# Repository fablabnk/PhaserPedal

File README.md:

This was a project to build a [Phaser Guitar Pedal from Instructables](https://www.instructables.com/Phaser-Guitar-Pedal/). 

As we attempted the project, we found that the build steps in the photos were incomplete, so it is actually impossible to place all components and make all the solder connections on the protoboard in the same way they did.

Our solution was to attempt to rework a new layout directly from the schematic in KiCad, partly as a learning experience in how to use KiCad at all. This involved:

- recreating the schematic in the schematic editor
- creating a board template in the pcb editor and placing components as similarly as possible to the original project
- routing the rats nest
- using the routings as a template for soldering

- some connections are done with solder bridges, some with wires - the wires are the traces - but how did we do solder bridges again?

The current state of the project is that the circuit doesn't work and we're not sure why. One wire got disconnected so this could help.

A possible next step could be to manufacture a PCB, but we have no guarantee that we routed it correctly or that the project even works in the first place.

So it would be better to go back to first principles to understand the concepts in the circuit

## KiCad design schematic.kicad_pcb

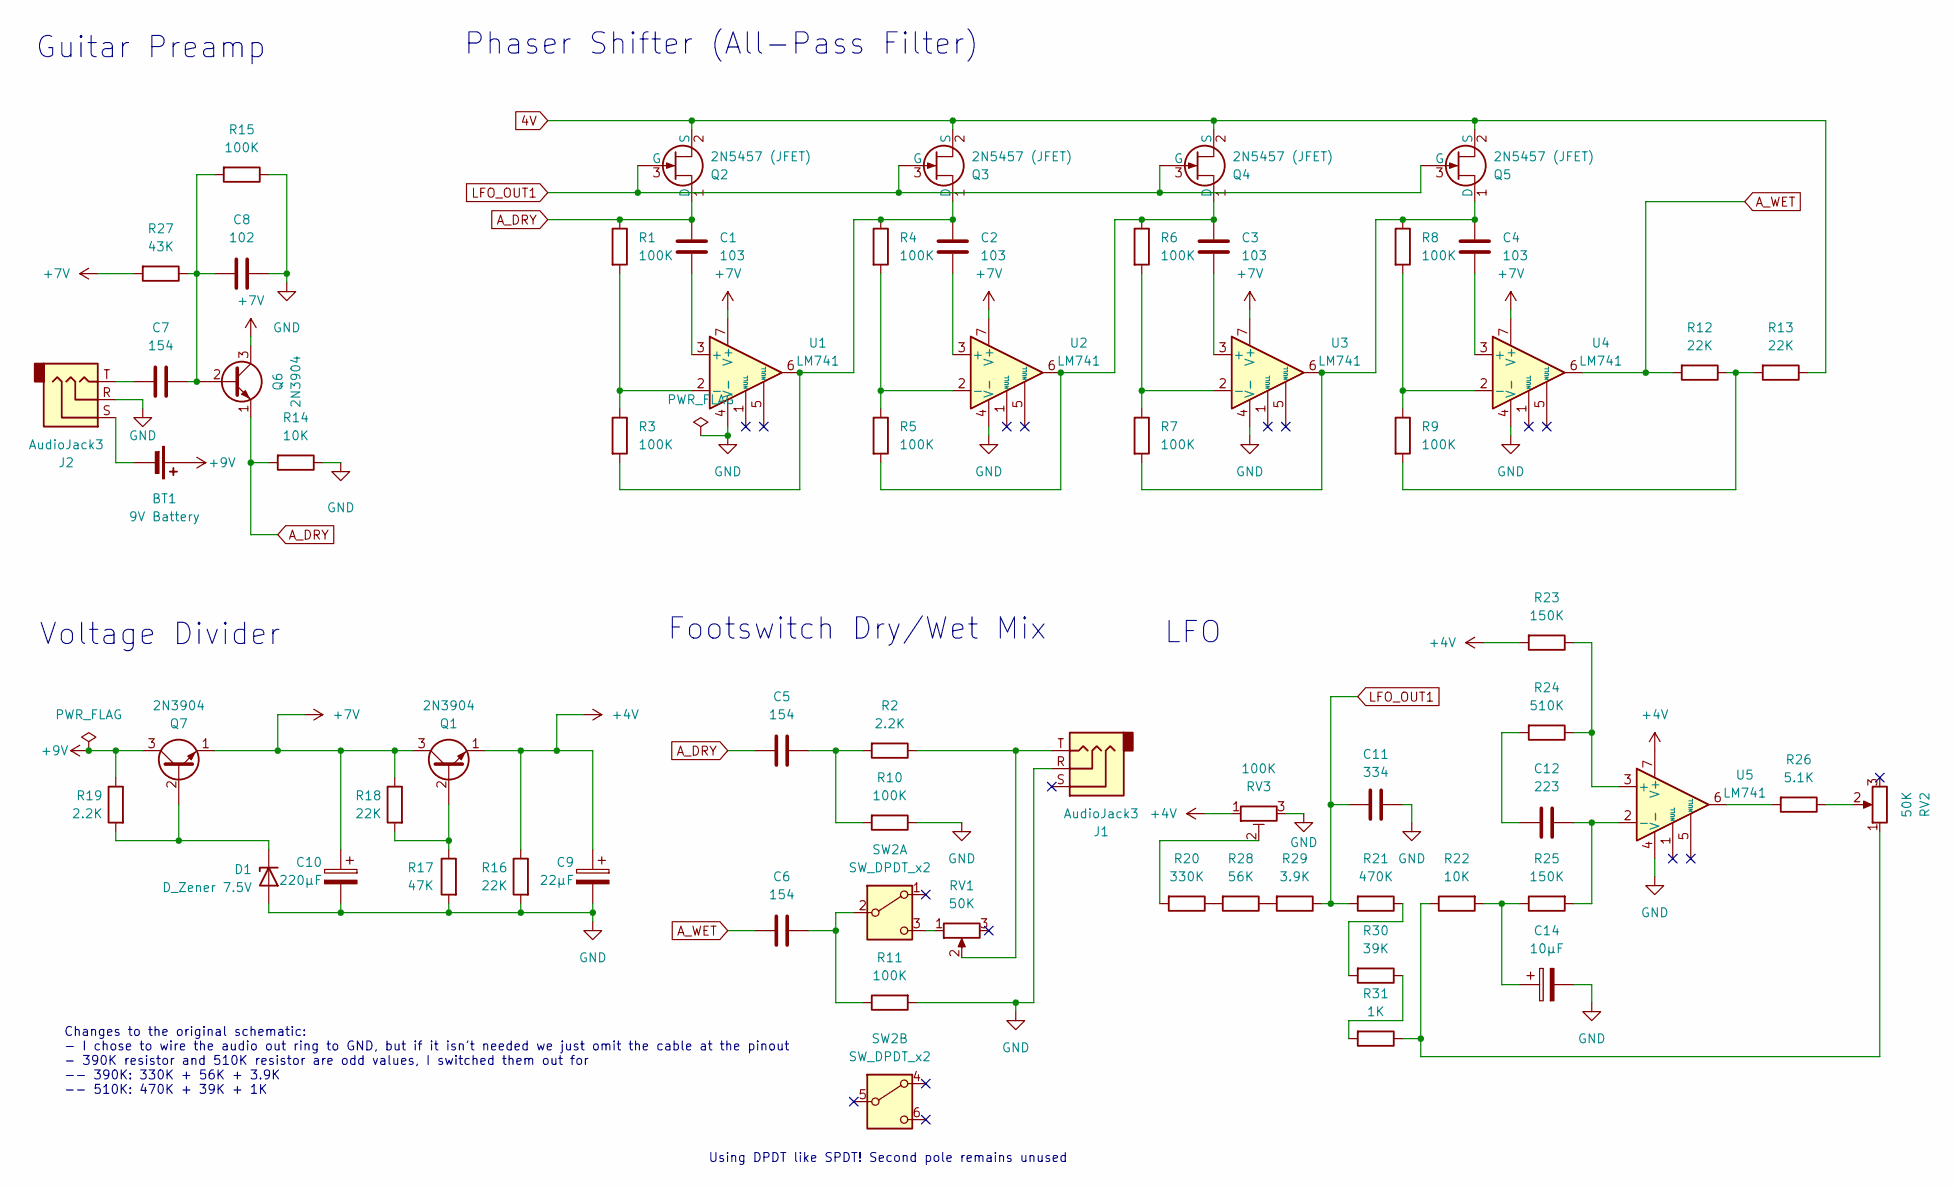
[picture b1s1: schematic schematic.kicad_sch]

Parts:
BT1: 9V Battery; PinHeader_1x02_P2.54mm_Vertical
C1, C2, C3, C4: 103; C_Axial_L5.1mm_D3.1mm_P7.50mm_Horizontal
C5, C6, C7: 154; C_Disc_D3.0mm_W1.6mm_P2.50mm
C8: 102; C_Axial_L5.1mm_D3.1mm_P7.50mm_Horizontal
C9: 22µF; CP_Radial_D5.0mm_P2.50mm
C10: 220µF; CP_Radial_D10.0mm_P5.00mm
C11: 334; C_Disc_D3.0mm_W1.6mm_P2.50mm
C12: 223; C_Axial_L5.1mm_D3.1mm_P7.50mm_Horizontal
C14: 10µF; CP_Radial_D5.0mm_P2.50mm
D1: D_Zener 7.5V; D_A-405_P7.62mm_Horizontal
J1: AudioJack3; PinHeader_1x02_P2.54mm_Vertical_TR
J2: AudioJack3; PinHeader_1x03_P2.54mm_Vertical_TRS
Q1, Q6, Q7: 2N3904; TO-92_Inline_Wide
Q2, Q3, Q4, Q5: 2N5457 (JFET); TO-92_Inline_Wide
R1, R3, R4, R5, R6, R7, R8, R9, R10, R11, R15: 100K; R_Axial_DIN0204_L3.6mm_D1.6mm_P5.08mm_Horizontal
R2, R19: 2.2K; R_Axial_DIN0204_L3.6mm_D1.6mm_P5.08mm_Horizontal
R12, R13, R16, R18: 22K; R_Axial_DIN0204_L3.6mm_D1.6mm_P5.08mm_Horizontal
R14, R22: 10K; R_Axial_DIN0204_L3.6mm_D1.6mm_P5.08mm_Horizontal
R17: 47K; R_Axial_DIN0204_L3.6mm_D1.6mm_P5.08mm_Horizontal
R20: 330K; R_Axial_DIN0204_L3.6mm_D1.6mm_P5.08mm_Horizontal
R21: 470K; R_Axial_DIN0204_L3.6mm_D1.6mm_P5.08mm_Horizontal
R23, R25: 150K; R_Axial_DIN0204_L3.6mm_D1.6mm_P5.08mm_Horizontal
R24: 510K; R_Axial_DIN0204_L3.6mm_D1.6mm_P5.08mm_Horizontal
R26: 5.1K; R_Axial_DIN0204_L3.6mm_D1.6mm_P5.08mm_Horizontal
R27: 43K; R_Axial_DIN0204_L3.6mm_D1.6mm_P5.08mm_Horizontal
R28: 56K; R_Axial_DIN0204_L3.6mm_D1.6mm_P5.08mm_Horizontal
R29: 3.9K; R_Axial_DIN0204_L3.6mm_D1.6mm_P5.08mm_Horizontal
R30: 39K; R_Axial_DIN0204_L3.6mm_D1.6mm_P5.08mm_Horizontal
R31: 1K; R_Axial_DIN0204_L3.6mm_D1.6mm_P5.08mm_Horizontal
RV1, RV2: 50K; PinHeader_1x02_P2.54mm_Vertical
RV3: 100K; Potentiometer_Bourns_3296Y_Vertical
SW2: SW_DPDT_x2; PinHeader_1x02_P2.54mm_Vertical_2_3
U1, U2, U3, U4, U5: LM741; DIP-8_W7.62mm_Socket

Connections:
4V: Q2.2 (S), Q3.2 (S), Q4.2 (S), Q5.2 (S), R13.1
+4V: C9.1, Q1.1 (E), R16.1, R23.2, RV3.1, U5.7 (V+)
+7V: C10.1, Q1.3 (C), Q6.3 (C), Q7.1 (E), R18.1, R27.2, U1.7 (V+), U2.7 (V+), U3.7 (V+), U4.7 (V+)
+9V: BT1.1 (+), Q7.3 (C), R19.1
A_DRY: C1.1, C5.2, Q2.1 (D), Q6.1 (E), R1.1, R14.2
A_WET: C6.1, R12.2, U4.6
GND: C8.1, C9.2, C10.2, C11.1, C14.2, D1.2 (A), J1.R, J2.R, R10.1, R11.2, R14.1, R15.1, R16.2, R17.2, RV3.3, U1.4 (V-), U2.4 (V-), U3.4 (V-), U4.4 (V-), U5.4 (V-)
LFO_OUT1: C11.2, Q2.3 (G), Q3.3 (G), Q4.3 (G), Q5.3 (G), R21.2, R29.1
unnamed: BT1.2 (-), J2.S
unnamed: C5.1, R2.2, R10.2
unnamed: C7.2, J2.T
unnamed: C12.2, R24.2
unnamed: C14.1, R22.2, R25.1
unnamed: D1.1 (K), Q7.2 (B), R19.2
unnamed: J1.T, R2.1, RV1.2
unnamed: Q1.2 (B), R17.1, R18.2
unnamed: C2.1, Q3.1 (D), R3.2, R4.1, U1.6
unnamed: C3.1, Q4.1 (D), R5.2, R6.1, U2.6
unnamed: C4.1, Q5.1 (D), R7.2, R8.1, U3.6
unnamed: C7.1, C8.2, Q6.2 (B), R15.2, R27.1
unnamed: R9.2, R12.1, R13.2
unnamed: R20.1, R28.2
unnamed: R20.2, RV3.2
unnamed: R21.1, R30.2
unnamed: R22.1, R31.1, RV2.1
unnamed: R26.1, RV2.2
unnamed: R26.2, U5.6
unnamed: R28.1, R29.2
unnamed: R30.1, R31.2
unnamed: C6.2, R11.1, SW2.2 (B)
unnamed: RV1.1, SW2.3 (C)
unnamed: C1.2, U1.3 (+)
unnamed: R1.2, R3.1, U1.2 (-)
unnamed: C2.2, U2.3 (+)
unnamed: R4.2, R5.1, U2.2 (-)
unnamed: C3.2, U3.3 (+)
unnamed: R6.2, R7.1, U3.2 (-)
unnamed: C4.2, U4.3 (+)
unnamed: R8.2, R9.1, U4.2 (-)
unnamed: R23.1, R24.1, U5.3 (+)
unnamed: C12.1, R25.2, U5.2 (-)

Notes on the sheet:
Using DPDT like SPDT! Second pole remains unused
Footswitch Dry/Wet Mix
Voltage Divider
Phaser Shifter (All-Pass Filter)
Guitar Preamp
LFO
Changes to the original schematic: - I chose to wire the audio out ring to GND, but if it isn't needed we just omit the cable at the pinout - 390K resistor and 510K resistor are odd values, I switched them out for -- 390K: 330K + 56K + 3.9K -- 510K: 470K + 39K + 1K

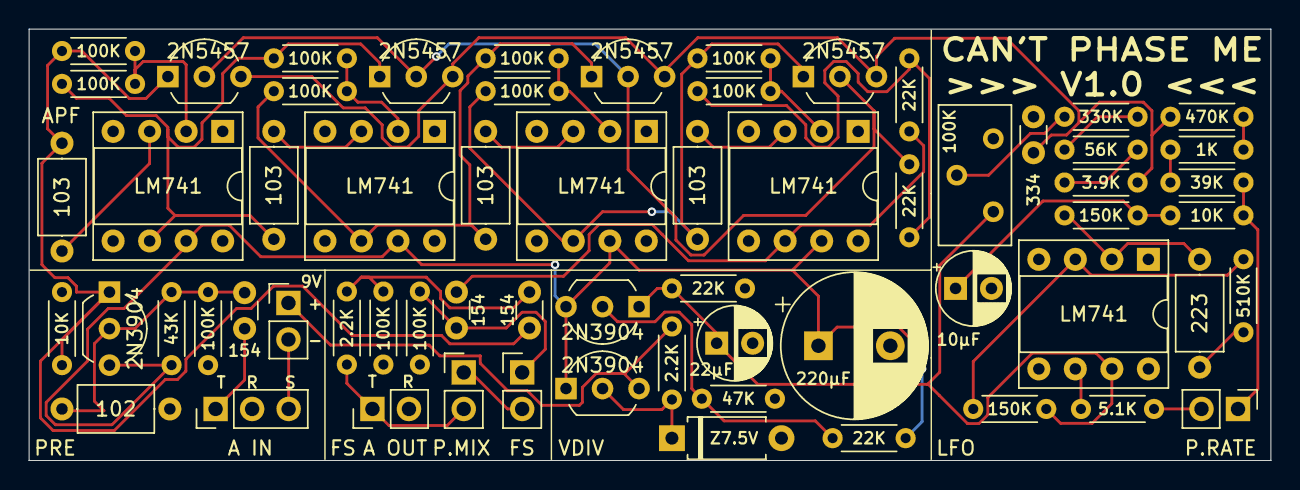
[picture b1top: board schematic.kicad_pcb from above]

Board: 2 copper layers, 86.4 x 30.0 mm, 64 parts (0 on the bottom side), 41 nets.

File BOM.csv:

"Id";"Designator";"Footprint";"Quantity";"Designation";"Supplier and ref";
1;"SW1";"PinHeader_1x02_P2.54mm_Vertical";1;"SW_SPST";;;
2;"J1";"PinHeader_1x02_P2.54mm_Vertical";1;"Audio  Out";;;
3;"D1";"D_A-405_P7.62mm_Horizontal";1;"D_Zener 7.5V";;;
4;"Q7,Q1,Q6";"TO-92_Inline_Wide";3;"2N3904";;;
5;"R21,R24";"R_Axial_DIN0207_L6.3mm_D2.5mm_P7.62mm_Horizontal";2;"510K";;;
6;"R22,R14";"R_Axial_DIN0207_L6.3mm_D2.5mm_P7.62mm_Horizontal";2;"10K";;;
7;"U1,U5,U4,U2,U3";"DIP-8_W7.62mm_Socket";5;"LM741";;;
8;"Q2,Q4,Q5,Q3";"TO-92_Inline_Wide";4;"2N5457 (JFET)";;;
9;"R15,R9,R4,R8,R11,R3,R1,R7,R6,R5,R10";"R_Axial_DIN0207_L6.3mm_D2.5mm_P7.62mm_Horizontal";11;"100K";;;
10;"C12";"C_Disc_D3.0mm_W1.6mm_P2.50mm";1;"223";;;
11;"R25,R23";"R_Axial_DIN0207_L6.3mm_D2.5mm_P7.62mm_Horizontal";2;"150K";;;
12;"C10";"CP_Radial_D10.0mm_P5.00mm";1;"220µF";;;
13;"C1,C2,C4,C3";"C_Disc_D3.0mm_W1.6mm_P2.50mm";4;"103";;;
14;"R18,R13,R16,R12";"R_Axial_DIN0207_L6.3mm_D2.5mm_P7.62mm_Horizontal";4;"22K";;;
15;"RV3";"Potentiometer_Runtron_RM-065_Vertical";1;"100K";;;
16;"RV2,RV1";"PinHeader_1x02_P2.54mm_Vertical";2;"50K";;;
17;"C5,C7,C6";"C_Disc_D3.0mm_W1.6mm_P2.50mm";3;"154";;;
18;"J4";"PinHeader_1x03_P2.54mm_Vertical";1;"Audio In";;;
19;"C11";"C_Disc_D3.0mm_W1.6mm_P2.50mm";1;"334";;;
20;"R19,R2";"R_Axial_DIN0207_L6.3mm_D2.5mm_P7.62mm_Horizontal";2;"2.2K";;;
21;"C8";"C_Disc_D3.0mm_W1.6mm_P2.50mm";1;"102";;;
22;"R20";"R_Axial_DIN0207_L6.3mm_D2.5mm_P7.62mm_Horizontal";1;"390K";;;
23;"R17";"R_Axial_DIN0207_L6.3mm_D2.5mm_P7.62mm_Horizontal";1;"47K";;;
24;"C9";"CP_Radial_D5.0mm_P2.50mm";1;"22µF";;;
25;"C14";"CP_Radial_D5.0mm_P2.50mm";1;"10µF";;;
26;"R26";"R_Axial_DIN0207_L6.3mm_D2.5mm_P7.62mm_Horizontal";1;"5.1K";;;
27;"R27";"R_Axial_DIN0207_L6.3mm_D2.5mm_P7.62mm_Horizontal";1;"43K";;;
28;"BT1";"PinHeader_1x02_P2.54mm_Vertical";1;"9V";;;

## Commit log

2024-04-04 moved all .md files to _notes folder
2024-04-04 added readme
2024-06-08 smaller redesign - ready to test laser cut
2024-06-08 added notes to CircuitInfo.md after laser cutteer test - also deleted duplicate unfinished project files
2024-06-15 pcb design now meets custom board rules for jlcpcb
